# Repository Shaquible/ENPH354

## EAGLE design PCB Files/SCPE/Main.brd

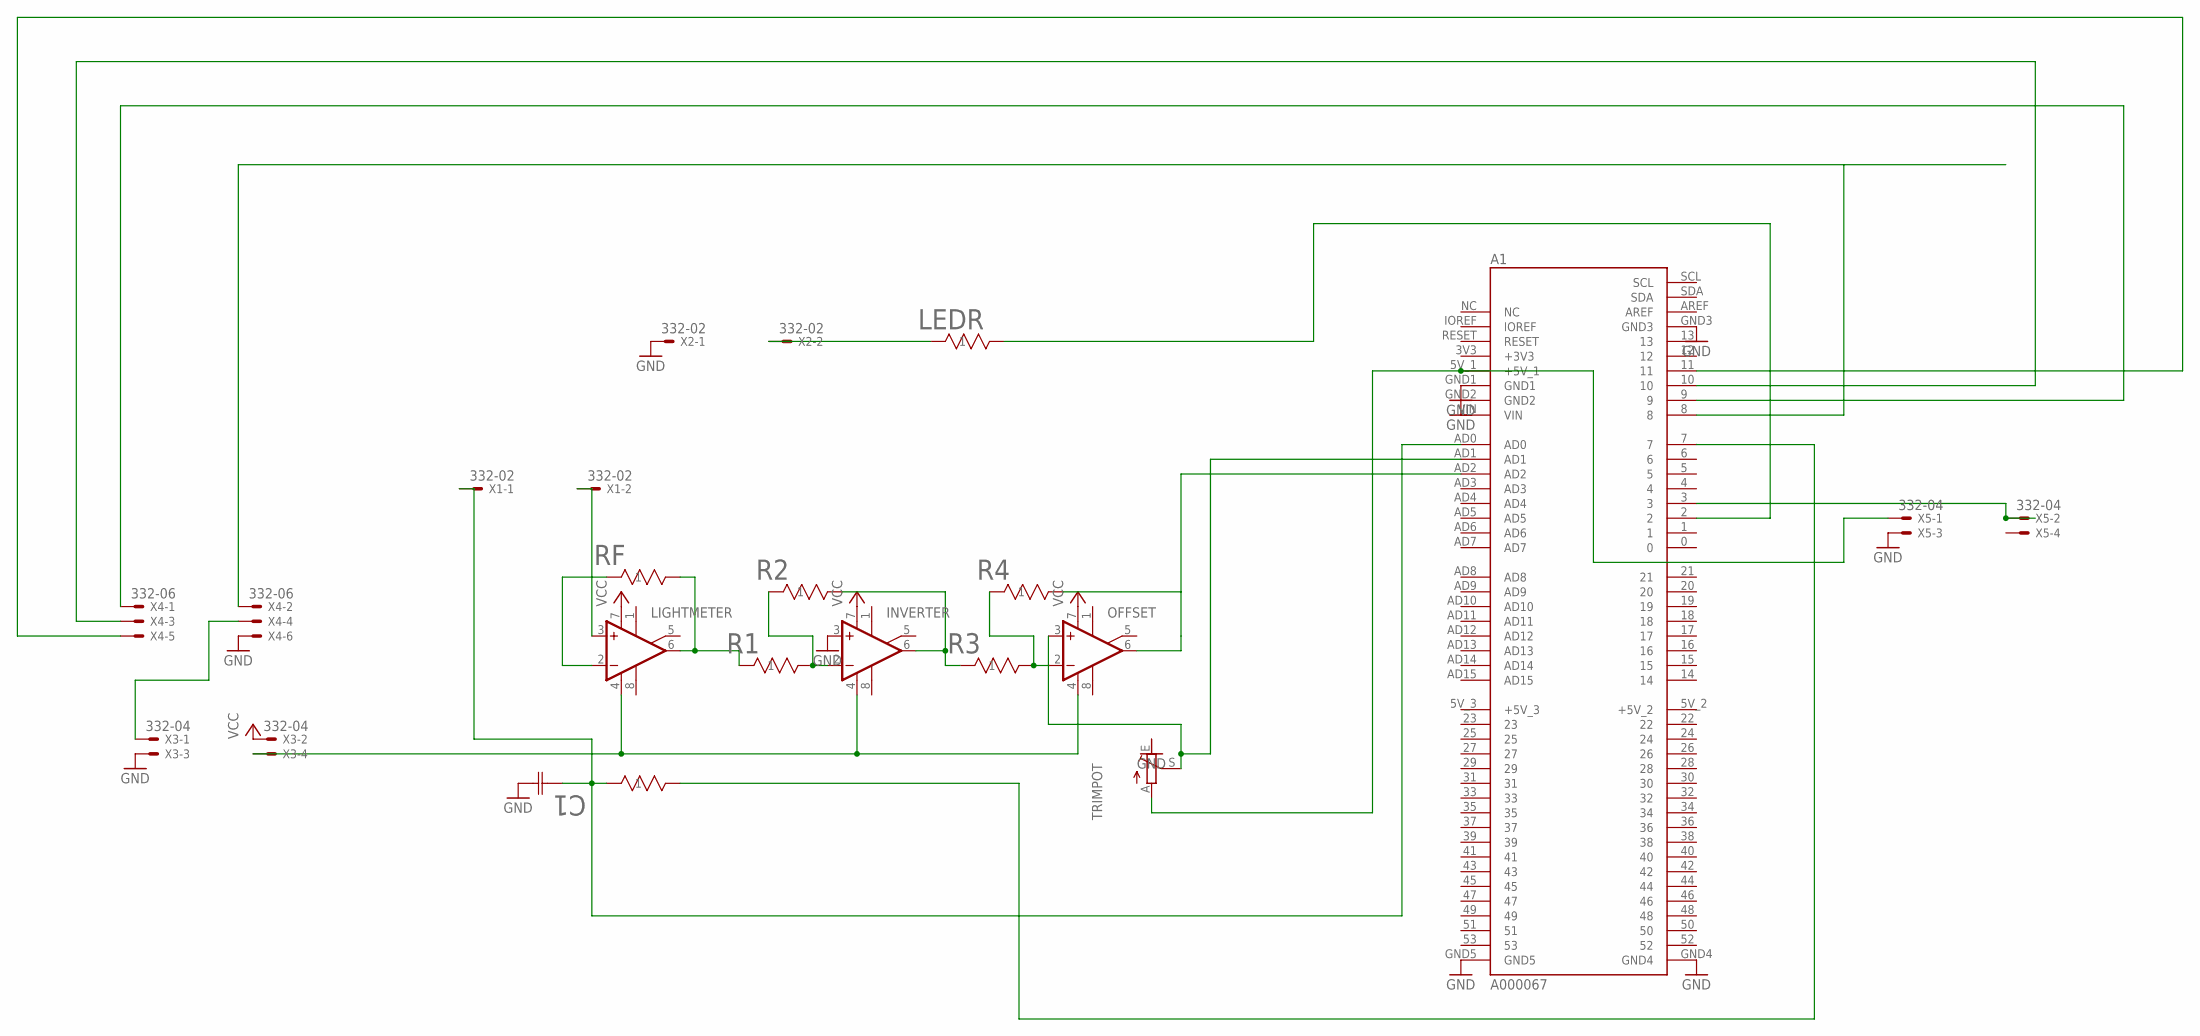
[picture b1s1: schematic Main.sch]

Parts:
A1: A000067; ARDUINO_A000067
C1: 50YXF470MEFCG412.5X20; CAP_YX_12P5X20_RUB
INVERTER: LM741P; DIL08
LEDR: RNF14FTD47K0; STA_RNF14_STP
LIGHTMETER: LM741P; DIL08
OFFSET: LM741P; DIL08
R1, R2, R3, R4: RNF14FTD47K0; STA_RNF14_STP
RCR: RNF14FTD47K0; STA_RNF14_STP
RF: RNF14FTD47K0; STA_RNF14_STP
TRIMPOT: TRIM_EU-B25V; B25V
X1, X2: 332-02
X3, X5: 332-04
X4: 332-06

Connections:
GND: A1.GND1, A1.GND2, A1.GND3, A1.GND4, A1.GND5, C1.2, INVERTER.3 (+IN), TRIMPOT.E, X2.1, X3.3, X4.6, X5.3
unnamed: A1.AD1, OFFSET.3 (+IN), TRIMPOT.S
unnamed: A1.AD0, C1.1, RCR.1, X1.1
unnamed: LIGHTMETER.2 (-IN), RF.1
unnamed: LIGHTMETER.6 (OUT), R1.1, RF.2
unnamed: INVERTER.2 (-IN), R1.2, R2.1
unnamed: A1.5V_1 (+5V_1), TRIMPOT.A, X5.1
unnamed: INVERTER.6 (OUT), R2.2, R3.1
unnamed: OFFSET.2 (-IN), R3.2, R4.1
unnamed: INVERTER.4 (V-), LIGHTMETER.4 (V-), OFFSET.4 (V-), X3.4
unnamed: A1.AD2, OFFSET.6 (OUT), R4.2
unnamed: LIGHTMETER.3 (+IN), X1.2
unnamed: A1.7, RCR.2
unnamed: A1.2, LEDR.2
unnamed: LEDR.1, X2.2
unnamed: X3.1, X4.4
unnamed: A1.8, X4.2
unnamed: A1.9, X4.1
unnamed: A1.10, X4.3
unnamed: A1.11, X4.5
unnamed: A1.3, X5.2
VCC: INVERTER.7 (V+), LIGHTMETER.7 (V+), OFFSET.7 (V+), X3.2

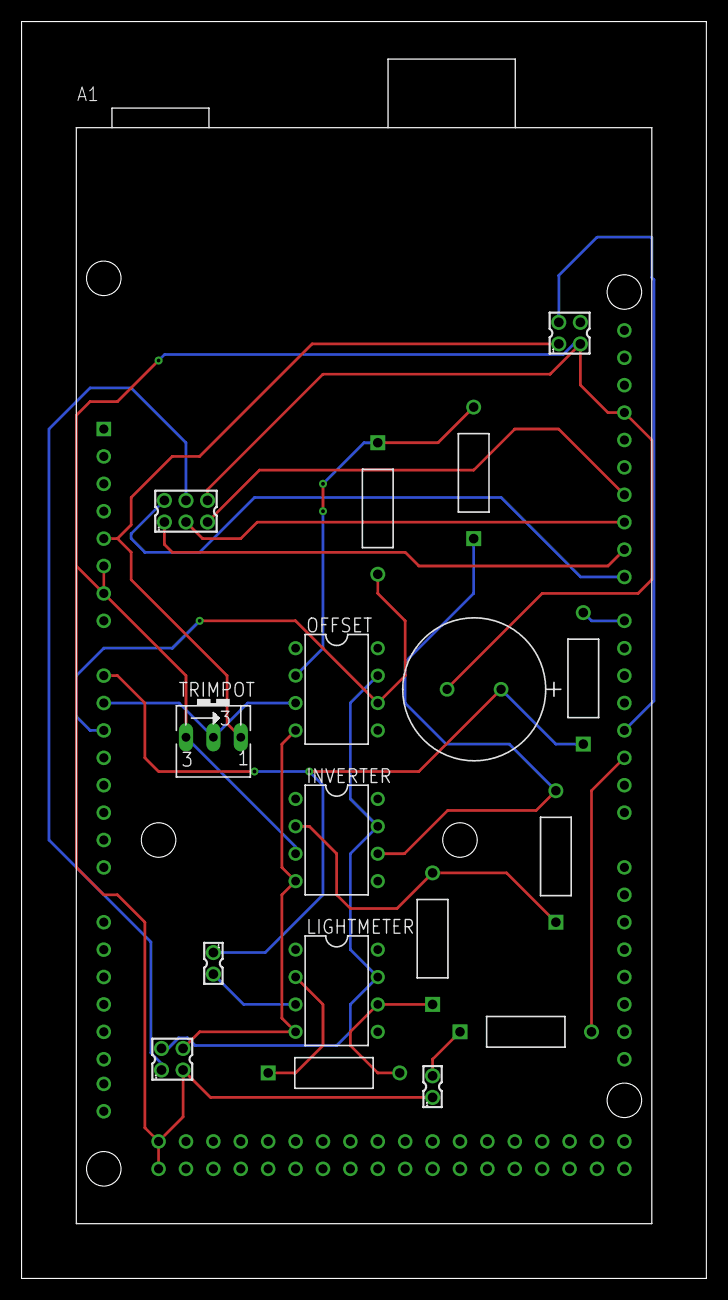
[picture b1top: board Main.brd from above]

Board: 2 copper layers, 63.5 x 116.5 mm, 18 parts (0 on the bottom side), 22 nets.

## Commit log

2023-02-28 first fdraft of SCPE
2023-03-01 worked on circuit simulations
2023-03-03 more SCPE improvements
2023-03-04 finished paramater extraction
2023-03-06 whole ton of work
2023-03-08 Re-structure and adding files
    Re-organized structure and added missing files like 3d parts, vis and .csvs
2023-03-08 calibration subVI
    calibration subVI created
2023-03-08 updated calibrate
    added input for offset angle
2023-03-08 worked on offset voltage
2023-03-12 did stuff
2023-03-12 done A43
2023-03-12 added part2 and data csvs
2023-03-12 finished Q4
2023-03-13 copy of Q3 to save data from 3b
2023-03-13 added new VI
2023-03-13 did q5
2023-03-13 fixed factor of 10 correction
2023-03-15 did measure voltage
2023-03-15 set bias voltage
2023-03-15 Finished Sweep VI
2023-03-15 moved folders
2023-03-15 worked on iv trace
2023-03-15 made VI to trigger all the sweeps
2023-03-16 added pcb files
2023-03-22 created the plate
2023-03-22 got iv trace working
2023-03-22 worked on integrating into main and the angle sweep\
2023-03-22 added delay in sweep
2023-03-22 worked more on main
2023-03-23 maybe fixed memory issue
2023-03-23 got angle sweep working correctly
2023-03-24 Fixed File Saving and added prev data functionality
2023-03-24 fixed buttons
2023-03-24 tested tracing and file saving
2023-03-29 Project Done
2023-04-05 added drawing plus new data
2023-04-05 completed plotting routine and plots
2023-04-06 better plots
2023-04-07 redid plots and improved SPCE
2023-04-07 Commented VIs
2023-04-11 3d part cad drawings
2023-04-11 added some comments
2023-04-11 zipped final VIs

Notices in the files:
parts and their libraries:
COPYRIGHT: Copyright (C) 2022 Ultra Librarian. All rights reserved.
